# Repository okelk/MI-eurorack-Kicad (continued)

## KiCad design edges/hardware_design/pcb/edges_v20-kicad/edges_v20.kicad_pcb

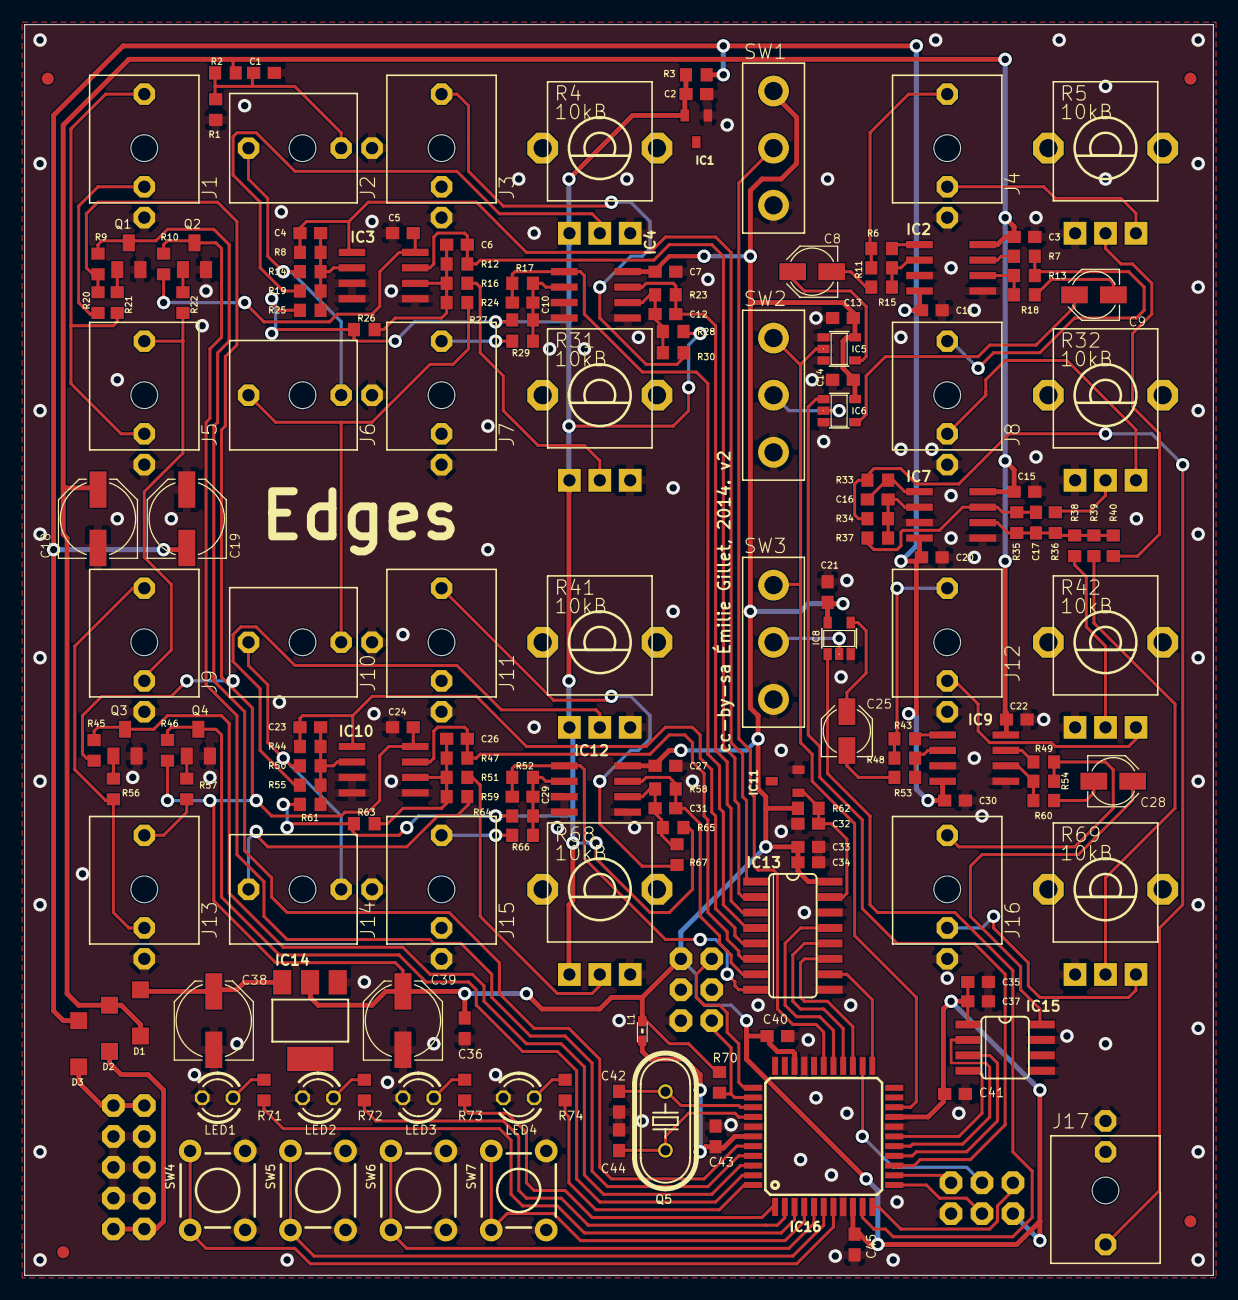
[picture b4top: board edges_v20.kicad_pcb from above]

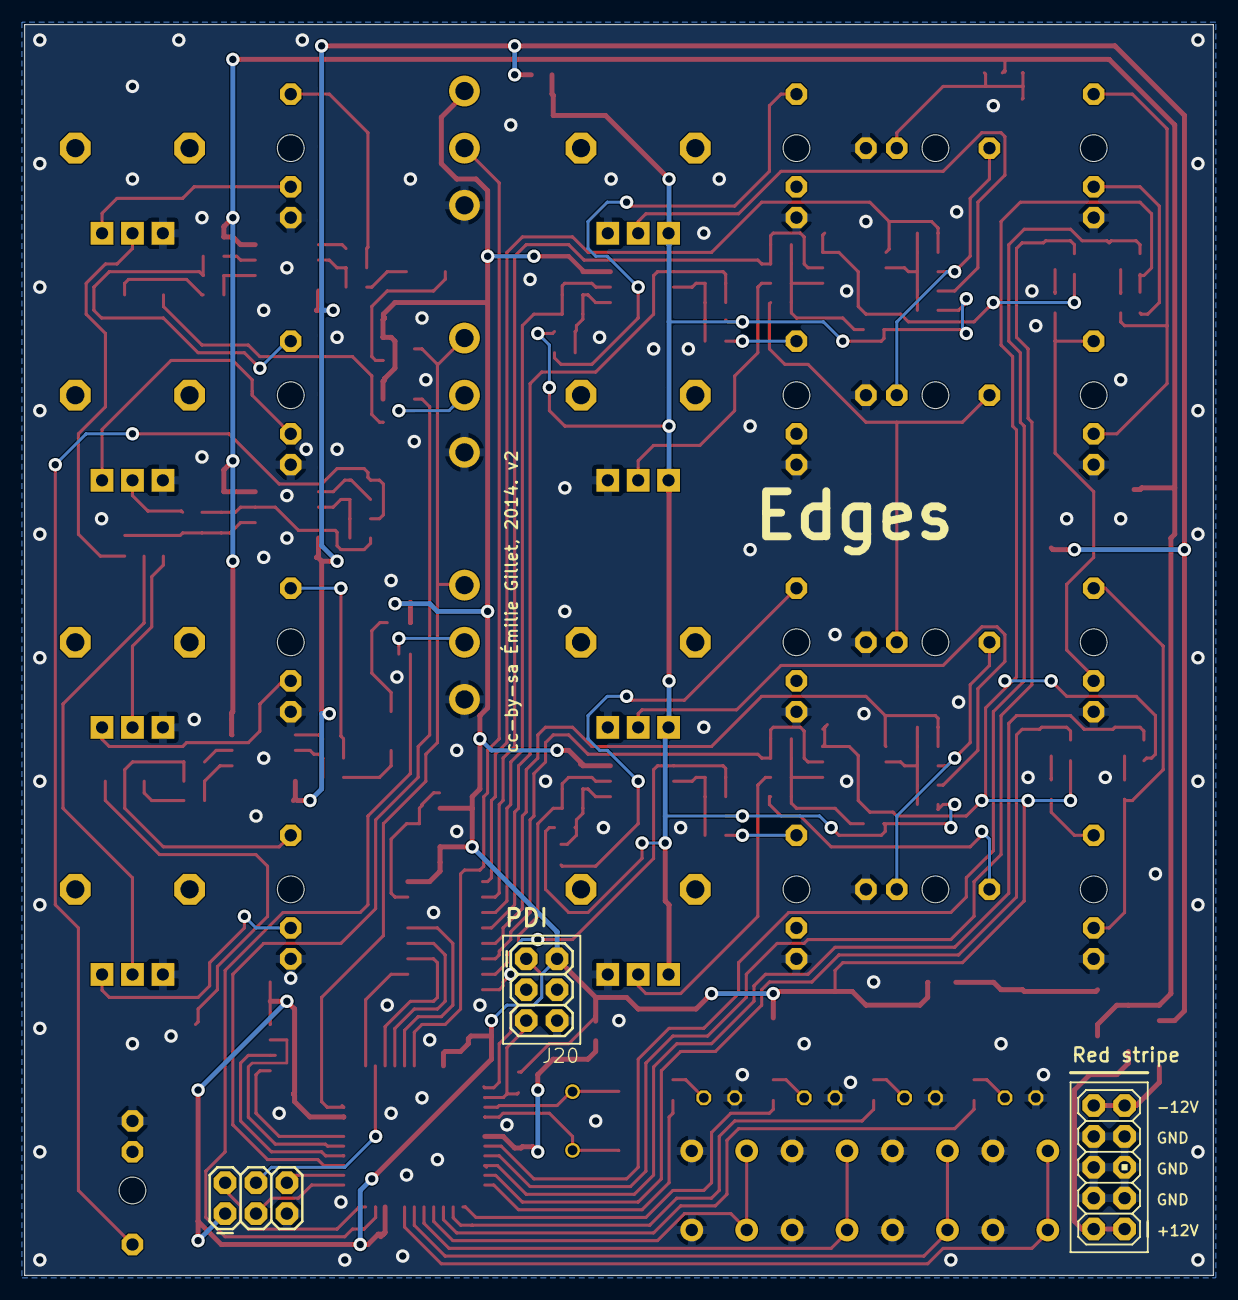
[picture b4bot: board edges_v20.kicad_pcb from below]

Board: 2 copper layers, 97.8 x 102.9 mm, 179 parts (3 on the bottom side), 118 nets.

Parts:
C1, C2, C32: 470n; C0603
C3, C5, C7, C11, C13, C14, C15, C20, C21, C22, C24, C27, C30, C34, C36, C37, C40, C41, C43, C45: 100n; C0603
C4, C6, C10, C12, C23, C26, C29, C31: 100p; C0603
C8, C9, C25, C28: 10u; PANASONIC_B
C16, C17, C42, C44: 18p; C0603
C18, C19, C38, C39: 47u; PANASONIC_D
C33, C35: 1u; C0603
D1, D2, D3: 1N5819HW; SOD123
IC1: LM4040 10V; DBZ_R-PDSO-G3
IC2, IC7, IC9: TL072D; SO08
IC3, IC4, IC10, IC12: MCP6002; SO08
IC5: 74AHC1G125DBV; SOT23-5
IC6, IC8: 74AHC1G86DBV; SOT23-5
IC11: LM4040B25; DBZ_R-PDSO-G3
IC13: MCP3208; SO16
IC14: LM1117-3.3; SOT223
IC15: MCP4822; SO08
IC16: ATXMEGA32A4U-AU; TQFP44
J1, J2, J3, J4, J5, J6, J7, J8, J9, J10, J11, J12, J13, J14, J15, J16, J17: PJ301_THONKICONN6; WQP_PJ_301M6
J18, J20: 2X3
J19: M05X2PTH; AVR_ICSP
JP1, JP2, JP3, JP4: FIDUCIAL1X2; FIDUCIAL-1X2
L1: 0603
LED1, LED2, LED3, LED4: LED3MM
Q1, Q2, Q3, Q4: MMBT3904; SOT23-BEC
Q5: 8MHz; HC49U70
R1: 2k; R0603
R2, R9, R10, R15, R18, R45, R46, R53, R60: 10k; R0603
R3: 300; R0603
R4, R5, R31, R32, R41, R42, R68, R69: 10kB; ALPS_POT_VERTICAL_PS
R6, R7, R20, R33, R43, R49, R62: 1k; R0603
R8, R12, R17, R23, R44, R47, R52, R58: 24.9k; R0603
R11, R13, R35, R48: 33k; R0603
R14, R21, R22, R24, R29, R30, R34, R36, R37, R38, R40, R50, R56, R57, R59, R66, R67: 100k; R0603
R16, R19, R25, R26, R27, R28, R51, R55, R61, R63, R64, R65: 200k; R0603
R39, R70: 39k; R0603
R54: 82k; R0603
R71, R72, R73, R74: 100; R0603
SW1, SW2, SW3: ES_100SP1T6B11M2QEH_SMALL
SW4, SW5, SW6, SW7: TACTILE-PTH

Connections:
+3V3: C5.1, C7.1, C13.1, C14.1, C21.1, C24.1, C27.1, C33.1, C34.1, C35.1, C36.1, C37.1, C39.+, C40.1, C41.1, C45.1, IC3.8, IC4.8, IC5.5, IC6.5, IC8.5, IC10.8, IC12.8, IC13.16, IC14.2, IC15.1, IC16.9, IC16.19, IC16.31, J18.1, J20.2, L1.1, R9.2, R10.2, R20.1, R45.2, R46.2, R62.1, R70.2, SW1.O
ADC_MISO: IC13.12, IC16.26
ADC_MOSI: IC13.11, IC16.25
ADC_SCK: IC13.13, IC16.27
ADC_SS: IC13.10, IC16.23
AREF: C32.1, IC11.1, IC13.15, R62.2
AREF_-10: C2.1, IC1.2, R3.2, R4.P$3, R25.1, R26.1, R27.1, R28.1, R31.P$3, R41.P$3, R61.1, R63.1, R64.1, R65.1, R68.P$3
CH1: C4.2, IC3.1, IC13.1, R8.2
CH2: C6.2, IC3.7, IC13.2, R12.2
CH3: C23.2, IC10.1, IC13.5, R44.2
CH4: C26.2, IC10.7, IC13.6, R47.2
CH5: C12.2, IC4.7, IC13.3, R23.2
CH6: C10.2, IC4.1, IC13.4, R17.2
CH7: C31.2, IC12.7, IC13.7, R58.2
CH8: C29.2, IC12.1, IC13.8, R52.2
CHANNEL1: C8.+, IC5.4
CHANNEL1_BUFFERED: J4.P3, R6.2, R11.2
CHANNEL1_RETURN: R5.P$2, R40.1
CHANNEL2: C9.+, IC6.4
CHANNEL2_BUFFERED: J8.P3, R7.2, R13.2
CHANNEL2_RETURN: R32.P$2, R36.1
CHANNEL3: C25.+, IC8.4
CHANNEL3_BUFFERED: J12.P3, R43.2, R48.2
CHANNEL3_RETURN: R38.1, R42.P$2
CHANNEL4: C28.+, IC15.8
CHANNEL4_BUFFERED: J16.P3, R49.2, R54.2
CHANNEL4_RETURN: R39.1, R69.P$2
COARSE1: R4.P$2, R19.1
COARSE2: R16.1, R31.P$2
COARSE3: R41.P$2, R55.1
COARSE4: R51.1, R68.P$2
CV1: J2.P3, J6.P2, R14.1
CV2: J6.P3, J10.P2, R24.1
CV3: J10.P3, J14.P2, R50.1
CV4: J14.P3, R59.1
DAC_MOSI: IC15.4, IC16.17
DAC_SCK: IC15.3, IC16.15
DAC_SS: IC15.2, IC16.16
FM1: J3.P3, R30.1
FM2: J7.P3, R29.1
FM3: J11.P3, R67.1
FM4: J15.P3, R66.1
GATE1: IC16.40, Q1.C, R9.1
GATE1_IN: J1.P3, J5.P2, R21.2
GATE1_LED: LED4.A, R74.2
GATE2: IC16.41, Q2.C, R10.1
GATE2_IN: J5.P3, J9.P2, R22.2
GATE2_LED: LED3.A, R73.2
GATE3: IC16.42, Q3.C, R45.1
GATE3_IN: J9.P3, J13.P2, R56.2
GATE3_LED: LED2.A, R72.2
GATE4: IC16.43, Q4.C, R46.1
GATE4_IN: J13.P3, R57.2
GATE4_LED: LED1.A, R71.2
GND: C1.2, C2.2, C3.2, C5.2, C7.2, C11.1, C13.2, C14.2, C15.2, C18.-, C19.+, C20.1, C21.2, C22.2, C24.2, C27.2, C30.1, C32.2, C33.2, C34.2, C35.2, C36.2, C37.2, C38.-, C39.-, C40.2, C41.2, C42.1, C43.2, C44.1, C45.2, IC1.1, IC2.3, IC2.5, IC3.3, IC3.4, IC3.5, IC4.3, IC4.4, IC4.5, IC5.1, IC5.3, IC6.3, IC7.3, IC7.5, IC8.3, IC9.3, IC9.5, IC10.3, IC10.4, IC10.5, IC11.2, IC12.3, IC12.4, IC12.5, IC13.9, IC13.14, IC14.1, IC15.5, IC15.7, IC16.8, IC16.18, IC16.30, IC16.38, J1.P1, J2.P1, J3.P1, J4.P1, J5.P1, J6.P1, J7.P1, J8.P1, J9.P1, J10.P1, J11.P1, J12.P1, J13.P1, J14.P1, J15.P1, J16.P1, J17.P1, J18.5, J19.3, J19.4, J19.5, J19.6, J19.7, J19.8, J20.6, LED1.K, LED2.K, LED3.K, LED4.K, Q1.E, Q2.E, Q3.E, Q4.E, R1.1, R4.P$1, R5.P$3, R31.P$1, R32.P$3, R41.P$1, R42.P$3, R68.P$1, R69.P$3, SW1.S, SW2.O, SW3.O, SW4.3, SW4.4, SW5.3, SW5.4, SW6.3, SW6.4, SW7.3, SW7.4
MIDI_IN: IC16.12, J18.3
MIX: J17.P3, R33.2, R34.2
unnamed: Q1.B, R21.1
unnamed: Q2.B, R22.1
unnamed: Q3.B, R56.1
unnamed: J8.P2, R32.P$1
unnamed: IC16.44, R74.1
unnamed: IC16.1, R73.1
unnamed: IC16.2, R72.1
unnamed: IC16.3, R71.1
unnamed: C23.1, IC10.2, R44.1, R50.2, R55.2, R61.2
unnamed: C10.1, IC4.2, R17.1, R27.2, R29.2
unnamed: J1.P2, R20.2
unnamed: C26.1, IC10.6, R47.1, R51.2, R59.2, R63.2
unnamed: C31.1, IC12.6, R58.1, R65.2, R67.2
unnamed: C29.1, IC12.2, R52.1, R64.2, R66.2
unnamed: IC6.1, IC16.14
unnamed: C8.-, R15.1
unnamed: IC8.2, SW3.P
unnamed: IC2.2, R11.1, R15.2
unnamed: IC2.1, R6.1
unnamed: IC6.2, SW2.P
unnamed: C9.-, R18.1
unnamed: IC2.6, R13.1, R18.2
unnamed: IC2.7, R7.1
unnamed: C25.-, R53.1
unnamed: C12.1, IC4.6, R23.1, R28.2, R30.2
unnamed: IC9.2, R48.1, R53.2
unnamed: IC9.1, R43.1
unnamed: C28.-, R60.1
unnamed: IC9.6, R54.1, R60.2
unnamed: IC9.7, R49.1
unnamed: C17.1, IC7.6, R35.1, R36.2, R38.2, R39.2, R40.2
unnamed: C16.1, IC7.2, R34.1, R37.2
unnamed: C16.2, IC7.1, R33.1
unnamed: C38.+, D1.C, IC14.3
unnamed: C43.1, IC16.39, L1.2
unnamed: J4.P2, R5.P$1
unnamed: IC8.1, IC16.10
unnamed: C17.2, IC7.7, R35.2, R37.1
unnamed: J12.P2, R42.P$1
unnamed: J16.P2, R69.P$1
unnamed: C6.1, IC3.6, R12.1, R16.2, R24.2, R26.2
unnamed: C1.1, J2.P2, R1.2, R2.1
unnamed: D2.A, J19.1, J19.2
unnamed: IC5.2, IC16.20, SW2.S, SW3.S
unnamed: D3.C, J19.9, J19.10
unnamed: C4.1, IC3.2, R8.1, R14.2, R19.2, R25.2
unnamed: C44.2, IC16.37, Q5.1
unnamed: C42.2, IC16.36, Q5.2
unnamed: Q4.B, R57.1
NES_TRIANGLE_CLK: IC16.24, J18.4
PDICLK: IC16.35, J20.5, R70.1
PDIDATA: IC16.34, J20.1
SW1: IC16.4, SW7.1, SW7.2
SW2: IC16.5, SW6.1, SW6.2
SW3: IC16.6, SW5.1, SW5.2
SW4: IC16.7, SW4.1, SW4.2
SW_MIDI_LEARN: IC16.11, J18.2
SW_MIDI_MODE: IC16.13, J18.6
SYNC_SWITCH: IC16.28, SW1.P
VCC: C3.1, C15.1, C18.+, C22.1, D1.A, D2.C, IC2.8, IC7.8, IC9.8, R2.2
VEE: C11.2, C19.-, C20.2, C30.2, D3.A, IC2.4, IC7.4, IC9.4, R3.1

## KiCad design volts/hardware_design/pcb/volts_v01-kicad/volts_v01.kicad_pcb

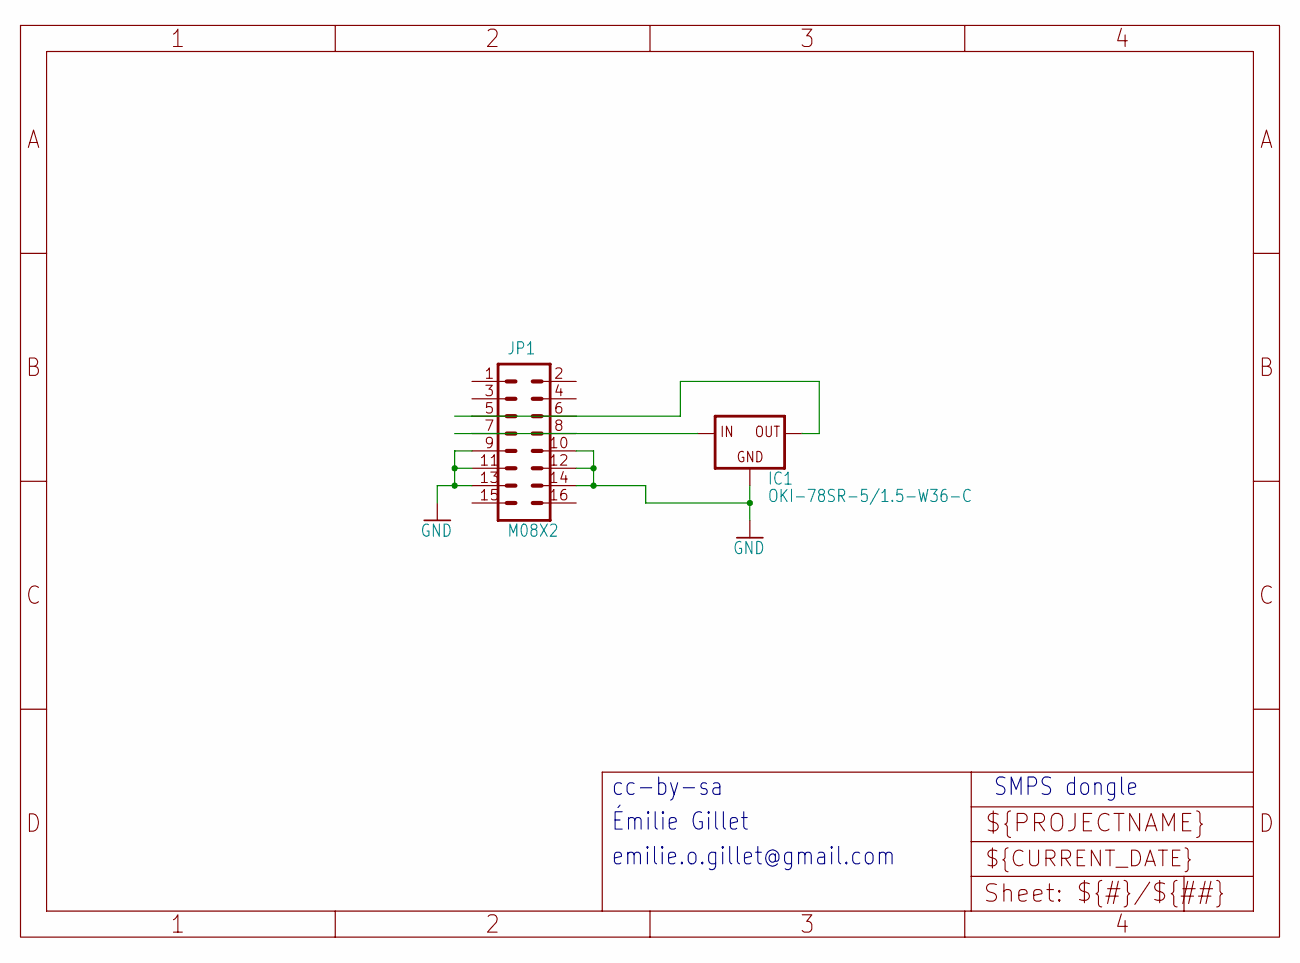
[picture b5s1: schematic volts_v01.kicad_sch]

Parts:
IC1: OKI-78SR-5/1.5-W36-C; OKI78SR
JP1: M08X2; 2X8

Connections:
GND: IC1.2 (GND), JP1.9, JP1.10, JP1.11, JP1.12, JP1.13, JP1.14
unnamed: IC1.1 (IN), JP1.7, JP1.8
unnamed: IC1.3 (OUT), JP1.5, JP1.6

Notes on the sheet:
Émilie Gillet
SMPS dongle
cc-by-sa
emilie.o.gillet@gmail.com

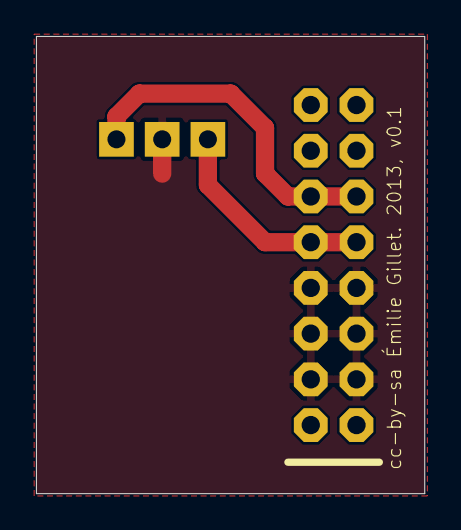
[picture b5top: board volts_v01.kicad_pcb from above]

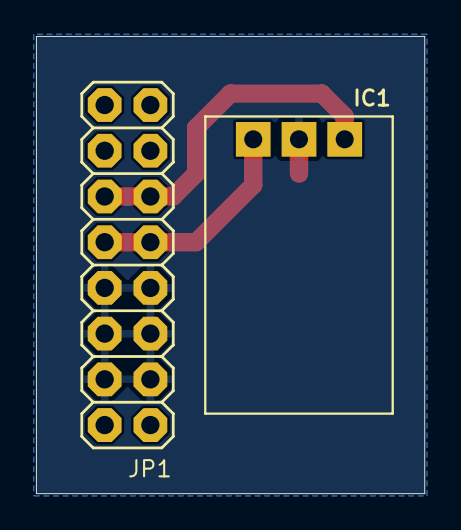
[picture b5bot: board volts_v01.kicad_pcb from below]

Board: 2 copper layers, 21.6 x 25.4 mm, 4 parts (2 on the bottom side), 3 nets.

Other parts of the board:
U$1: LOGO_5VOLTS
U$2: LOGO_5VOLTS_EDIT

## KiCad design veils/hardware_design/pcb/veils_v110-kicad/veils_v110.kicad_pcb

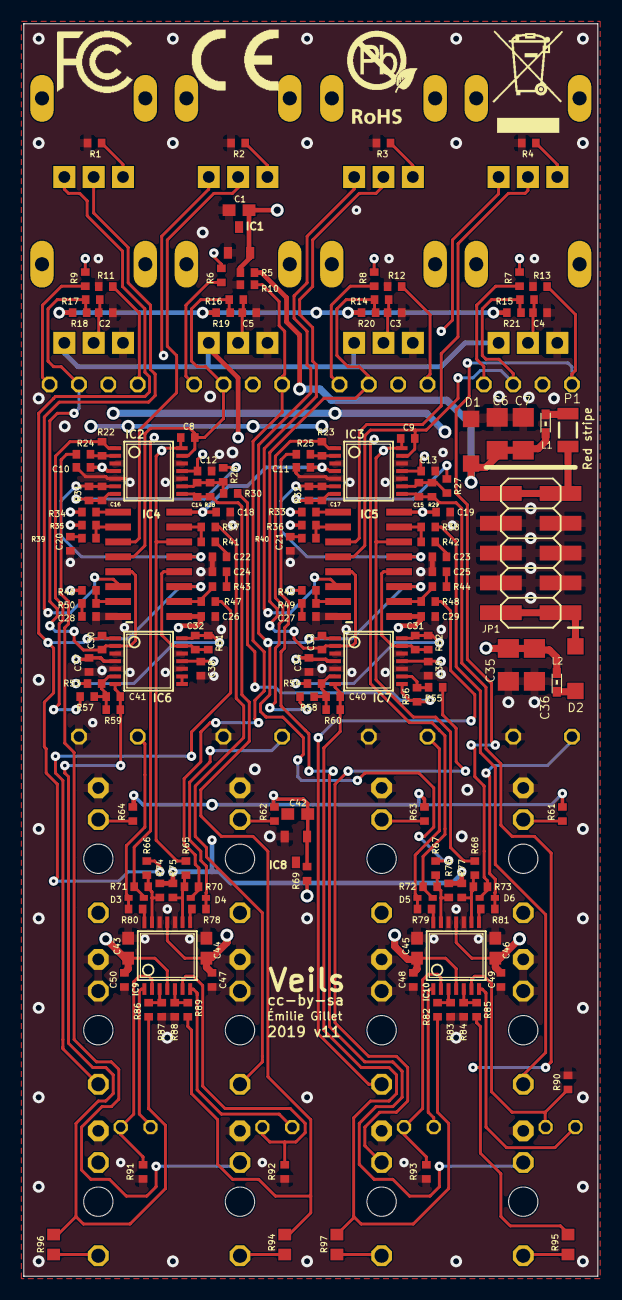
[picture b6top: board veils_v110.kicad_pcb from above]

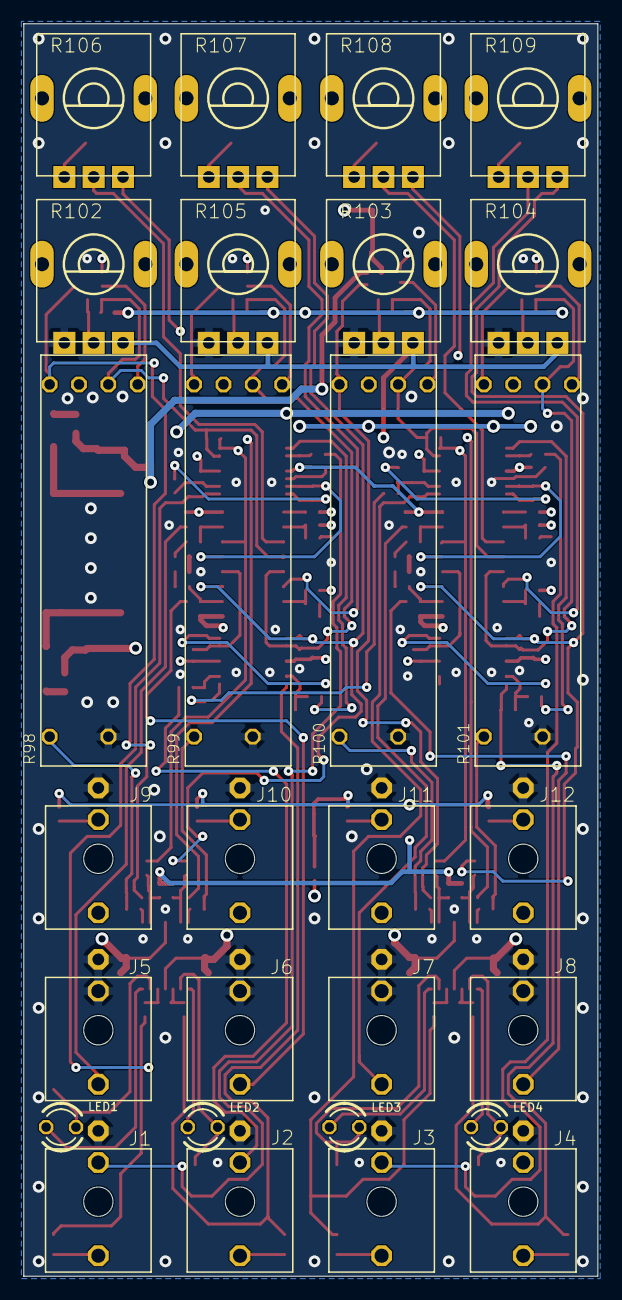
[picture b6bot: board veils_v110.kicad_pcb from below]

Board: 4 copper layers, 48.9 x 106.7 mm, 199 parts (28 on the bottom side), 121 nets.

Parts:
C1, C42, C43, C44, C45, C46: 2.2u; C0603
C2, C3, C4, C5, C10, C11, C12, C13, C18, C19, C26, C29, C34, C37, C38, C39, C47, C48, C49, C50: 100n; C0402
C6, C7, C35, C36: 22u; C1206
C8, C9, C14, C15, C16, C17, C30, C31, C32, C33, C40, C41: 100p; C0402
C20, C21, C22, C23, C24, C25, C27, C28: 560p; C0402
D1, D2: 1N5819HW; SOD123
D3, D4, D5, D6: 1N4148; SOD523
IC1: LM4040B25; DBZ_R-PDSO-G3
IC2, IC3, IC6, IC7: OPA1679; TSSOP14_065
IC4, IC5: V2164SZ; SOIC16N
IC8: LM4040B10; DBZ_R-PDSO-G3
IC9, IC10: LM324PW; TSSOP14_065
J1, J2, J3, J4, J5, J6, J7, J8, J9, J10, J11, J12: PJ301_THONKICONNTME; WQP_PJ_301M_TME
JP1: M05X2SMD; 2X5-SMD
L1, L2: 742792664; 0603
LED1, LED2, LED3, LED4: 3BC-F; LED3MM
P1: PTCSMD; PTC-1206
R1, R2, R3, R4: 2.0k; R0402
R5, R10, R11, R12, R13, R61, R62, R63, R64, R78, R79, R80, R81: 24.9k; R0402
R6, R7, R8, R9: 100k; R0402
R14, R15, R16, R17: 120k; R0402
R18, R19, R20, R21: 20M; R0402
R22, R23, R56: 5.6k; R0402
R24, R25, R26, R27, R28, R29, R30, R53, R54, R55, R57, R58, R59, R60: 5.1k; R0402
R31, R32, R35, R36, R37, R38, R45, R46, R47, R48, R51, R52: 49.9k; R0402
R33, R34: 680k; R0402
R39, R40, R41, R42, R43, R44, R49, R50, R69: 510; R0402
R65, R66, R67, R68, R70, R71, R72, R73, R74, R75, R76, R77, R82, R83, R84, R85, R86, R87, R88, R89: 1.0M; R0402
R90, R91, R92, R93: 1.2k; R0402
R94, R95, R96, R97: 510; R0603
R98, R99, R100, R101: 20kB; BOURNS_SLIDER
R102, R103, R104, R105: 50kB; ALPS_POT_NARROW
R106, R107, R108, R109: 10kB; ALPS_POT_NARROW
U$1: CE_MEDIUM
U$2: FCC_MEDIUM
U$3: ROHS_LOGO
U$4: TRASHCAN_LOGO

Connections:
1_TO_2: IC3.1, R23.1, R58.2
2_TO_3: IC7.8, R30.2, R56.1
3_TO_4: IC2.1, R22.1, R57.2
AREF_+10: C42.1, IC8.1, R61.2, R62.2, R63.2, R64.2, R69.2, R102.P$1, R103.P$1, R104.P$1, R105.P$1
AREF_-2.5: C1.1, IC1.2, R5.2, R18.2, R19.2, R20.2, R21.2, R35.2, R36.2, R45.2, R46.2, R74.1, R75.1, R76.1, R77.1
CV_IN_1: J9.P3, R7.2
FOO: IC5.2, R36.1, R40.2
FOO1: IC5.7, R45.1, R49.2
FOO2: IC4.2, R35.1, R39.2
FOO3: IC4.7, R46.1, R50.2
GND: C1.2, C2.2, C3.2, C4.2, C5.2, C6.1, C7.1, C10.2, C11.2, C12.1, C13.1, C18.2, C19.2, C20.2, C21.2, C22.2, C23.2, C24.2, C25.2, C26.1, C27.2, C28.2, C29.1, C34.2, C35.2, C36.2, C37.2, C38.1, C39.1, C42.2, C43.2, C44.1, C45.2, C46.1, C47.1, C48.2, C49.1, C50.2, D1.C, IC1.1, IC2.3, IC2.5, IC2.10, IC2.12, IC3.3, IC3.5, IC3.10, IC3.12, IC4.8, IC5.8, IC6.3, IC6.5, IC6.10, IC6.12, IC7.3, IC7.5, IC7.10, IC7.12, IC8.2, IC9.10, IC9.12, IC10.10, IC10.12, J1.P1, J2.P1, J3.P1, J4.P1, J5.P1, J5.P2, J6.P1, J6.P2, J7.P1, J7.P2, J8.P1, J8.P2, J9.P1, J10.P1, J11.P1, J12.P1, JP1.3, JP1.4, JP1.5, JP1.6, JP1.7, JP1.8, R1.1, R2.1, R3.1, R4.1, R10.2, R11.2, R12.2, R13.2, R83.1, R84.1, R87.1, R88.1, R90.2, R91.2, R92.2, R93.2, R98.3, R99.3, R100.3, R101.3, R102.P$3, R103.P$3, R104.P$3, R105.P$3
unnamed: IC10.5, R84.2, R85.2
unnamed: IC6.8, IC6.9
unnamed: J6.P3, R48.2
unnamed: IC10.3, R82.2, R83.2
unnamed: IC9.5, R88.2, R89.2
unnamed: J2.P3, R97.1
unnamed: J1.P3, R95.1
unnamed: IC9.3, R86.2, R87.2
unnamed: IC5.3, R106.P$2
unnamed: C15.1, IC3.9, R27.1, R29.2
unnamed: D2.A, JP1.1, JP1.2
unnamed: JP1.9, JP1.10, P1.2
unnamed: L1.2, P1.1
unnamed: C4.1, R15.2, R102.P$2
unnamed: R4.2, R106.P$3
unnamed: D2.C, L2.2
unnamed: C25.1, R44.1
unnamed: IC10.7, LED1.K
unnamed: IC10.6, LED1.A, R90.1
unnamed: C21.1, R40.1
unnamed: J10.P2, R63.1
unnamed: IC3.2, R23.2, R25.1
unnamed: J3.P3, R94.1
unnamed: IC5.10, R44.2, R48.1
unnamed: J1.P2, R25.2
unnamed: IC5.6, R107.P$2
unnamed: C40.1, IC7.6, R54.1, R58.1, R60.2
unnamed: IC5.1, R33.2
unnamed: IC4.3, R108.P$2
unnamed: J9.P2, R61.1
unnamed: R7.1, R98.2
unnamed: R3.2, R107.P$3
unnamed: R8.1, R99.2
unnamed: R2.2, R108.P$3
unnamed: IC10.1, LED2.K
unnamed: IC10.2, LED2.A, R93.1
unnamed: IC7.9, R55.1, R56.2
unnamed: J2.P2, R55.2
unnamed: C31.2, IC7.14, R52.1, R54.2
unnamed: J10.P3, R8.2
unnamed: C27.1, R49.1
unnamed: C33.1, IC5.5, IC7.2, R14.1, R20.1, R99.1
unnamed: IC4.6, R109.P$2
unnamed: J11.P3, R6.2
unnamed: C22.1, R41.1
unnamed: IC4.15, R37.1, R41.2
unnamed: C23.1, R42.1
unnamed: J12.P2, R64.1
unnamed: C14.1, IC2.9, R26.1, R28.2, R30.1
unnamed: IC10.8, R81.1
unnamed: R1.2, R109.P$3
unnamed: J7.P3, R37.2
unnamed: C31.1, IC5.12, IC7.13, R52.2
unnamed: D6.A, R13.1, R73.2, R98.E
unnamed: J12.P3, R9.2
unnamed: C16.1, IC2.6, IC4.13, R31.2
unnamed: IC10.9, R68.2, R73.1, R77.2
unnamed: IC9.7, LED3.K
unnamed: IC9.6, LED3.A, R92.1
unnamed: IC2.2, R22.2, R24.1
unnamed: J3.P2, R24.2
unnamed: C32.1, IC4.12, IC6.13, R51.2
unnamed: C20.1, R39.1
unnamed: R6.1, R100.2
unnamed: C9.1, IC3.13, IC5.4, R15.1, R21.1, R98.1
unnamed: J5.P3, R38.2
unnamed: C8.1, IC2.13, IC4.4, R16.1, R19.1, R100.1
unnamed: D5.A, R12.1, R72.2, R99.E
unnamed: J8.P3, R47.2
unnamed: R9.1, R101.2
unnamed: J4.P3, R96.1
unnamed: C24.1, R43.1
unnamed: IC4.10, R43.2, R47.1
unnamed: IC10.14, R79.1
unnamed: IC5.15, R38.1, R42.2
unnamed: C41.1, IC6.6, R53.1, R57.1, R59.2
unnamed: C9.2, IC3.14, IC5.14, R68.1, R106.P$1
unnamed: IC10.13, R67.2, R72.1, R76.2
unnamed: IC9.8, R78.1
unnamed: C33.2, IC5.11, IC7.1, R67.1, R107.P$1
unnamed: IC4.1, R34.2
unnamed: D4.A, R10.1, R70.2, R100.E
unnamed: IC9.9, R65.2, R70.1, R75.2
unnamed: IC9.1, LED4.K
unnamed: IC9.2, LED4.A, R91.1
unnamed: IC9.14, R80.1
unnamed: C8.2, IC2.14, IC4.14, R65.1, R108.P$1
unnamed: C32.2, IC6.14, R51.1, R53.2
unnamed: J11.P2, R62.1
unnamed: C28.1, R50.1
unnamed: C30.1, IC4.5, IC6.2, R17.1, R18.1, R101.1
unnamed: D3.A, R11.1, R71.2, R101.E
unnamed: IC9.13, R66.2, R71.1, R74.2
unnamed: C30.2, IC4.11, IC6.1, R66.1, R109.P$1
unnamed: C17.1, IC3.6, IC5.13, R32.2
unnamed: C17.2, IC3.7, R27.2, R32.1
unnamed: C3.1, R14.2, R105.P$2
unnamed: C5.1, R16.2, R103.P$2
unnamed: C16.2, IC2.7, R26.2, R31.1
unnamed: C2.1, R17.2, R104.P$2
OUT1: C15.2, IC3.8, R29.1, R85.1, R95.2
OUT2: C40.2, IC7.7, R60.1, R82.1, R97.2
OUT3: C14.2, IC2.8, R28.1, R89.1, R94.2
OUT4: C41.2, IC6.7, R59.1, R86.1, R96.2
PROT1: D6.C, R81.2, R98.B
PROT2: D5.C, R79.2, R99.B
PROT3: D4.C, R78.2, R100.B
PROT4: D3.C, R80.2, R101.B
VCC: C10.1, C11.1, C18.1, C19.1, C34.1, C35.1, C36.1, C37.1, C43.1, C45.1, C48.1, C50.1, IC2.4, IC3.4, IC4.16, IC5.16, IC6.4, IC7.4, IC9.4, IC10.4, L2.1, R33.1, R34.1, R69.1
VEE: C6.2, C7.2, C12.2, C13.2, C26.2, C29.2, C38.2, C39.2, C44.2, C46.2, C47.2, C49.2, D1.A, IC2.11, IC3.11, IC4.9, IC5.9, IC6.11, IC7.11, IC9.11, IC10.11, L1.1, R5.1

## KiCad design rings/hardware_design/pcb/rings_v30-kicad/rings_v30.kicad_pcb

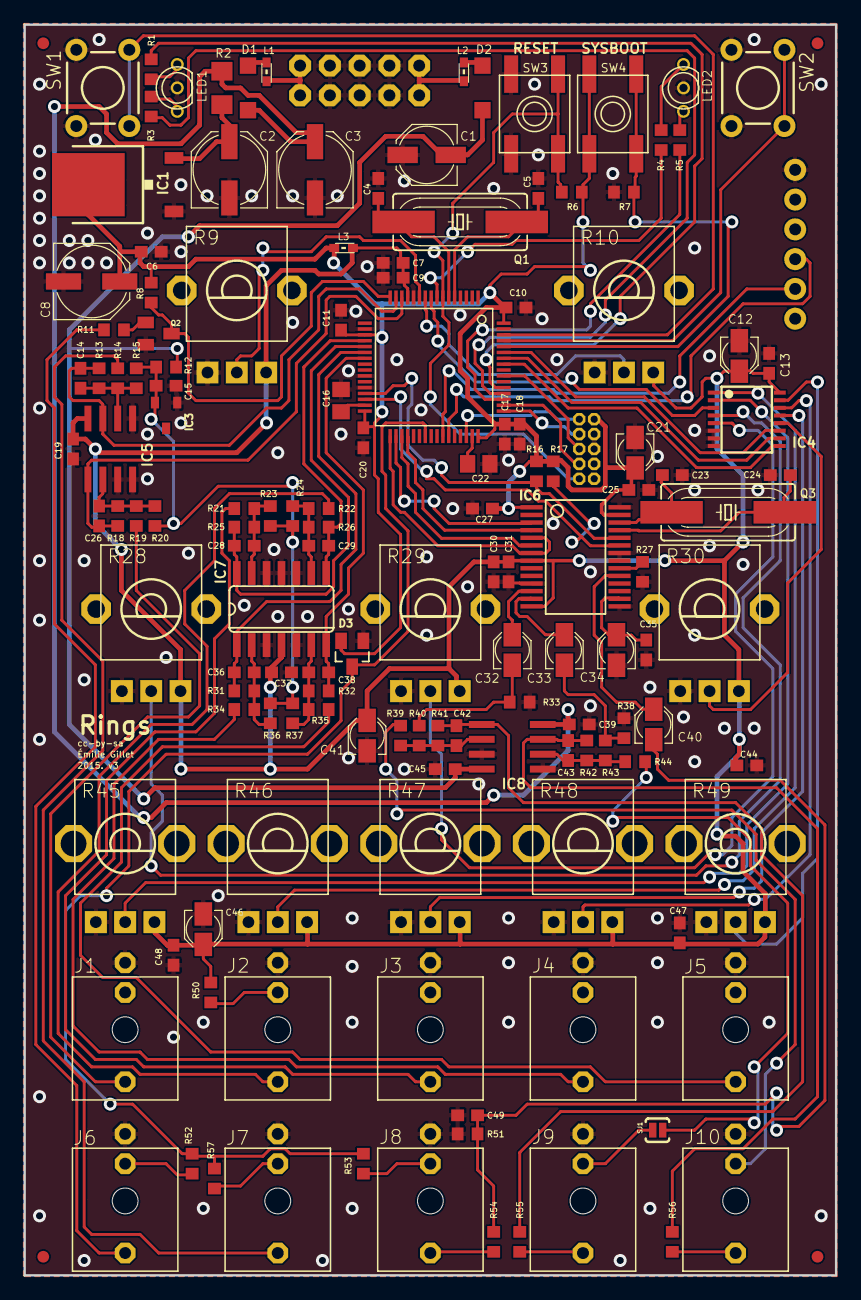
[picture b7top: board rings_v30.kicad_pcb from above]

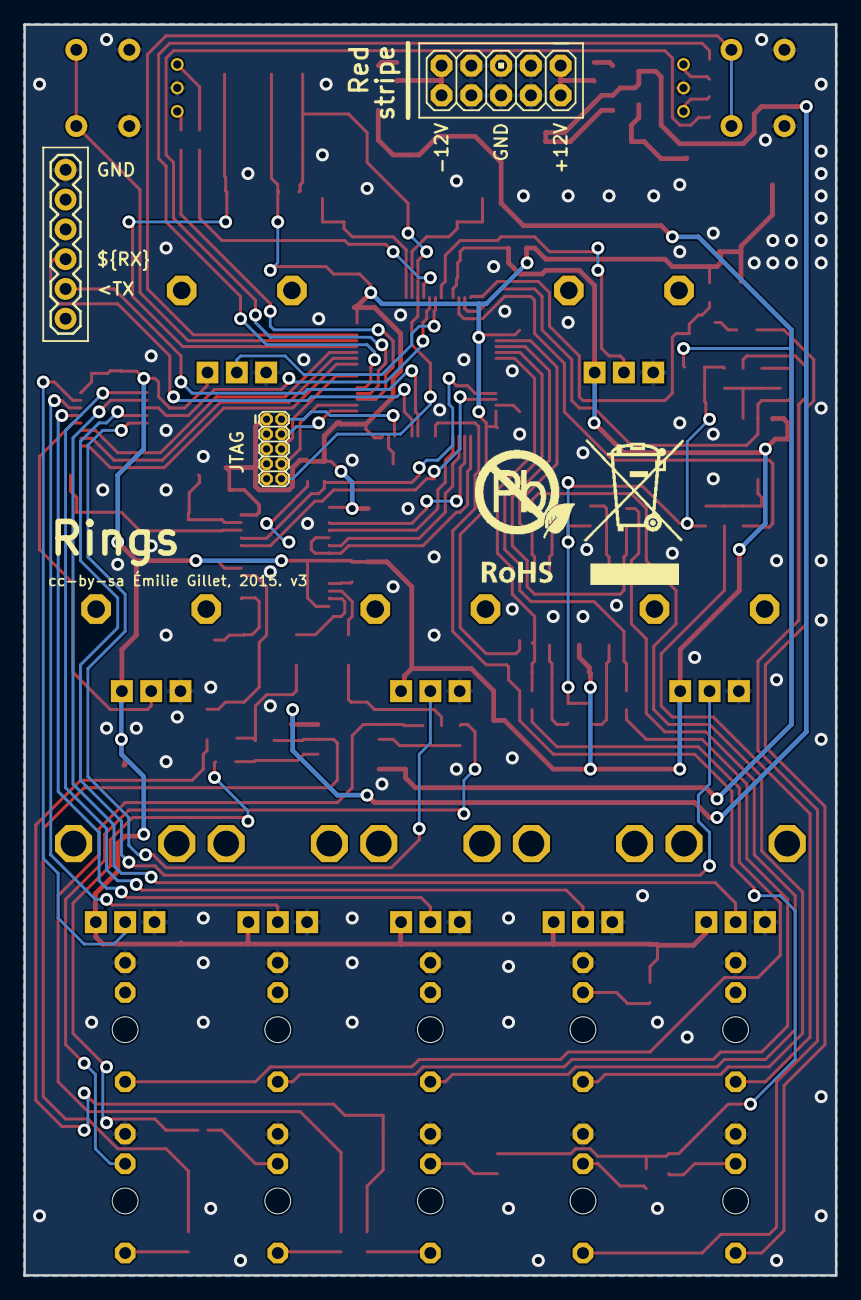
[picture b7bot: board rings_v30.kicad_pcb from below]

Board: 2 copper layers, 69.2 x 106.7 mm, 148 parts (4 on the bottom side), 99 nets.

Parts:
C1: 22u; PANASONIC_C
C2, C3, C8: 47u; PANASONIC_D
C4, C5, C23, C24, C42, C43: 18p; C0603
C6, C9, C10, C11, C13, C15, C17, C19, C20, C25, C27, C31, C35, C37, C39, C44, C45, C47, C48: 100n; C0603
C7, C18, C30: 1u; C0603
C12, C21, C32, C33, C34, C40, C41, C46: 10u; PANASONIC_A
C14, C29: 2.2n; C0603
C16, C22: 2.2u; C0805
C26, C28, C36, C38: 10n; C0603
C49: 220p; C0603
D1, D2: 1N5819HW; SOD123
D3: BAT54S; SOT23
F1, F2, F3, F4: FIDUCIAL1X2; FIDUCIAL-1X2
IC1: LM1117-3.3; TO252
IC2: STM32F405RGT6; TQFP-10X10-64
IC3: LM4040B10; DBZ_R-PDSO-G3
IC4: 4051PW; TSSOP16
IC5: MCP6002; SO08
IC6: WM8731; SSOP28
IC7: MCP6004; SO14
IC8: TL072; SO08
J1, J2, J3, J4, J5, J6, J7, J8, J9, J10: PJ301_THONKICONN6; WQP_PJ_301M6
JP1: M05X2MINIJTAG; 2X5-1.27
JP2: 1X06
JP3: M05X2PTH; AVR_ICSP
L1, L2, L3: 0603
LED1, LED2: WP115VEGW; LED-BICOLOR-THROUGHHOLE
Q1: 8MHz; HC49UP
Q2: MMBT3904; SOT23-BEC
Q3: 12.288MHz; HC49UP
R1, R3, R4, R5: 180; R0603
R2: 4.7; R1206
R6, R7, R8: 10k; R0603
R9, R10, R28, R29, R30: 10kB; ALPS_POT_VERTICAL_PS
R11, R14, R19, R21, R22, R34, R35, R52: 100k; R0603
R12, R16, R17: 2.2k; R0603
R13, R33, R38, R39, R41, R42, R44: 47k; R0603
R15: 180k; R0603
R18, R25, R26, R31, R32: 20k; R0603
R20, R23, R24, R36, R37: 120k; R0603
R27, R54: 36k; R0603
R40, R43, R51: 6.8k; R0603
R45, R46, R47, R48, R49: 10kB; ALPS_POT_VERTICAL
R50: 3.3M; R0603
R53: 1M; R0603
R55, R56: 1.0k; R0603
R57: 470k; R0603
SJ1: SOLDERJUMPERNC2; SJ_2S-NOTRACE
SW1, SW2: TACTILE-PTH
SW3, SW4: EVQ-Q2
U$2: ROHS_BIG

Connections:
+3V3: C6.1, C8.+, C10.1, C11.1, C17.1, C18.1, C20.1, C21.+, C25.1, C27.1, D3.2, IC1.3, IC2.19, IC2.32, IC2.48, IC2.64, IC6.1, IC6.27, JP1.1, L3.1, R6.2, R8.2, R16.2, R17.2, SW4.B, SW4.B'
+3V3_A: C7.1, C9.1, C12.+, C13.1, C19.1, C30.1, C31.1, C37.1, C41.+, C44.1, C46.+, C47.1, C48.1, IC2.13, IC4.16, IC5.8, IC6.8, IC6.14, IC7.4, L3.2, R9.P$1, R10.P$1, R28.P$1, R29.P$1, R30.P$1, R45.P$1, R46.P$1, R47.P$1, R48.P$1, R49.P$1, R50.2
AREF_-10: C15.1, IC3.2, R12.2, R15.2, R20.2, R23.2, R24.2, R36.2, R37.2
AUX_OUT: C33.+, IC6.13
BOOT_FLASH: IC2.60, R7.2, SW4.A, SW4.A'
BRIGHTNESS_ATT: IC4.2, R45.P$2
BRIGHTNESS_CV: C26.2, IC2.14, IC5.1, R18.1
BRIGHTNESS_POT: IC4.4, R28.P$2
CV_NORMALIZATION: J7.P2, R57.2
DAMP_ATT: IC4.13, R47.P$2
DAMP_CV: C28.2, IC2.21, IC7.14, R25.1
DAMP_POT: IC4.5, R29.P$2
FM_CV: C29.2, IC2.20, IC7.8, R26.1
FREQUENCY_ATT: IC4.1, R46.P$2
FREQUENCY_POT: IC2.11, R9.P$2
GEOMETRY_ATT: IC4.14, R48.P$2
GEOMETRY_CV: C36.2, IC2.22, IC7.1, R31.1
GEOMETRY_POT: IC2.10, R10.P$2
GND: C1.+, C2.-, C3.-, C4.1, C5.1, C6.2, C7.2, C8.-, C9.2, C10.2, C11.2, C12.-, C13.2, C15.2, C16.2, C17.2, C18.2, C19.2, C20.2, C21.-, C22.2, C23.1, C24.1, C25.2, C27.2, C30.2, C31.2, C34.-, C35.2, C37.2, C39.2, C41.-, C44.2, C45.1, C46.-, C47.2, C48.2, C49.2, D3.1, IC1.1, IC2.12, IC2.18, IC2.26, IC2.28, IC2.63, IC3.1, IC4.6, IC4.7, IC4.8, IC5.3, IC5.4, IC5.5, IC6.11, IC6.15, IC6.21, IC6.22, IC6.28, IC7.3, IC7.5, IC7.10, IC7.11, IC7.12, IC8.3, IC8.5, J1.P1, J2.P1, J3.P1, J4.P1, J5.P1, J6.P1, J7.P1, J8.P1, J9.P1, J10.P1, JP1.3, JP1.5, JP1.9, JP2.1, JP3.3, JP3.4, JP3.5, JP3.6, JP3.7, JP3.8, LED1.2, LED2.2, Q2.E, R7.1, R9.P$3, R10.P$3, R27.2, R28.P$3, R29.P$3, R30.P$3, R33.1, R38.1, R45.P$3, R46.P$3, R47.P$3, R48.P$3, R49.P$3, R51.1, SW1.1, SW1.2, SW2.1, SW2.2, SW3.A, SW3.A'
I2C_SCL: IC2.29, IC6.24, R16.1
I2C_SDA: IC2.30, IC6.23, R17.1
I2S_LRCK: IC2.33, IC6.5, IC6.7
I2S_SCK: IC2.34, IC6.3
I2S_SIN: IC2.35, IC6.6
I2S_SOUT: IC2.36, IC6.4
IN_1: IC6.20, R27.1
IN_2: C40.+, IC6.19
JTCK: IC2.49, JP1.4
JTDI: IC2.50, JP1.8
JTDO: IC2.55, JP1.6
JTMS: IC2.46, JP1.2
MAIN_OUT: C32.+, IC6.12
MUXED_POTS: IC2.9, IC4.3
MUX_ADDR_0: IC2.59, IC4.11
MUX_ADDR_1: IC2.58, IC4.10
MUX_ADDR_2: IC2.57, IC4.9
unnamed: J1.P3, R19.2
unnamed: C26.1, IC5.2, R18.2, R19.1, R20.1
unnamed: J7.P3, R14.2
unnamed: J2.P3, R22.2
unnamed: C29.1, IC7.9, R22.1, R24.1, R26.2
unnamed: J4.P3, R34.2
unnamed: C5.2, IC2.5, Q1.2
unnamed: C4.2, IC2.6, Q1.1
unnamed: J6.P3, R11.1
unnamed: J3.P3, R21.2
unnamed: C28.1, IC7.13, R21.1, R23.1, R25.2
unnamed: LED1.3, R1.2
unnamed: C22.1, IC2.47
unnamed: C14.1, IC5.6, R13.2, R14.1, R15.1
unnamed: C36.1, IC7.2, R31.2, R34.1, R36.1
unnamed: C2.+, IC1.2, R2.1
unnamed: C34.+, C35.1, IC6.16
unnamed: C40.-, C49.1, R51.2, R54.1
unnamed: C16.1, IC2.31
unnamed: J6.P2, R52.2
unnamed: J8.P3, R54.2
unnamed: LED1.1, R3.2
unnamed: C33.-, R38.2, R43.2
unnamed: D1.A, L1.1
unnamed: C43.1, IC8.6, R42.2, R43.1, R44.1
unnamed: J5.P3, R35.2
unnamed: LED2.3, R4.2
unnamed: C43.2, IC8.7, R42.1, R56.2
unnamed: J10.P3, R56.1
unnamed: C38.1, IC7.6, R32.2, R35.1, R37.1
unnamed: C32.-, R33.2, R40.2
unnamed: C42.1, IC8.2, R39.1, R40.1, R41.2
unnamed: C42.2, IC8.1, R41.1, R55.2
unnamed: J9.P3, R55.1
unnamed: LED2.1, R5.2
unnamed: D2.C, L2.1
unnamed: IC2.52, R3.1
unnamed: J2.P2, R50.1
unnamed: J8.P2, R53.2
unnamed: IC2.8, R4.1
unnamed: C24.2, IC6.25, Q3.2
unnamed: C23.2, IC6.26, Q3.1
unnamed: IC2.53, R1.1
unnamed: IC2.51, R5.1
unnamed: J10.P2, R39.2
unnamed: R44.2, SJ1.1
unnamed: J9.P2, SJ1.2
unnamed: JP3.1, JP3.2, L1.2
unnamed: JP3.9, JP3.10, L2.2
unnamed: Q2.B, R11.2
NORMALIZATION_PROBE: D3.3, IC2.39, R52.1, R53.1, R57.1
POSITION_ATT: IC4.15, R49.P$2
POSITION_CV: C38.2, IC2.23, IC7.7, R32.1
POSITION_POT: IC4.12, R30.P$2
RESET: IC2.7, JP1.10, R6.1, SW3.B, SW3.B'
RX: IC2.43, JP2.4
STRUM: IC2.16, Q2.C, R8.1
SW_MODE: IC2.61, SW2.3, SW2.4
SW_POLYPHONY: IC2.62, SW1.3, SW1.4
TX: IC2.42, JP2.5
VCC: C3.+, C39.1, D1.C, IC8.8, R2.2
VEE: C1.-, C45.2, D2.A, IC8.4, R12.1
V_OCT_CV: C14.2, IC2.15, IC5.7, R13.1
